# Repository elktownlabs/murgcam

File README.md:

# murgcam
Autonomous, time-based, low power still camera.

The first instance of this camera in action:
https://wwv-schwarzwald.de/die-murg/cam

## Project description
This repo documents Hard- and Software for a very low-power, battery/solar powered camera with GSM/LTE connectivity.
It is designed to operate unattended for months in an off-grid environment.
It will upload images to a server on a time-based trigger.

The intended use-case is to monitor river-waterlevels for whitewater paddlers. 
The advantage of a camera over other gauging techniques 
is, only line-of sight is needed, no access to the Water.
Being diectly at the water brings legal and mechanical challenginges that are not at play using a camera.

Full discussion of the original design decisions here:
https://elktown-labs.com/autonomouscam/

## Status
The repo just transferred from non-public to public, we try to add more documentation.
Currently, work is going on for a new hardware revision with a few improvements, most notably upgrading to a LTE capable Modem.

## Participation welcome
If you are interested in building / operating such a camera or want to contribute to it's development,
feel free to open an [issue](https://github.com/elktownlabs/murgcam/issues).

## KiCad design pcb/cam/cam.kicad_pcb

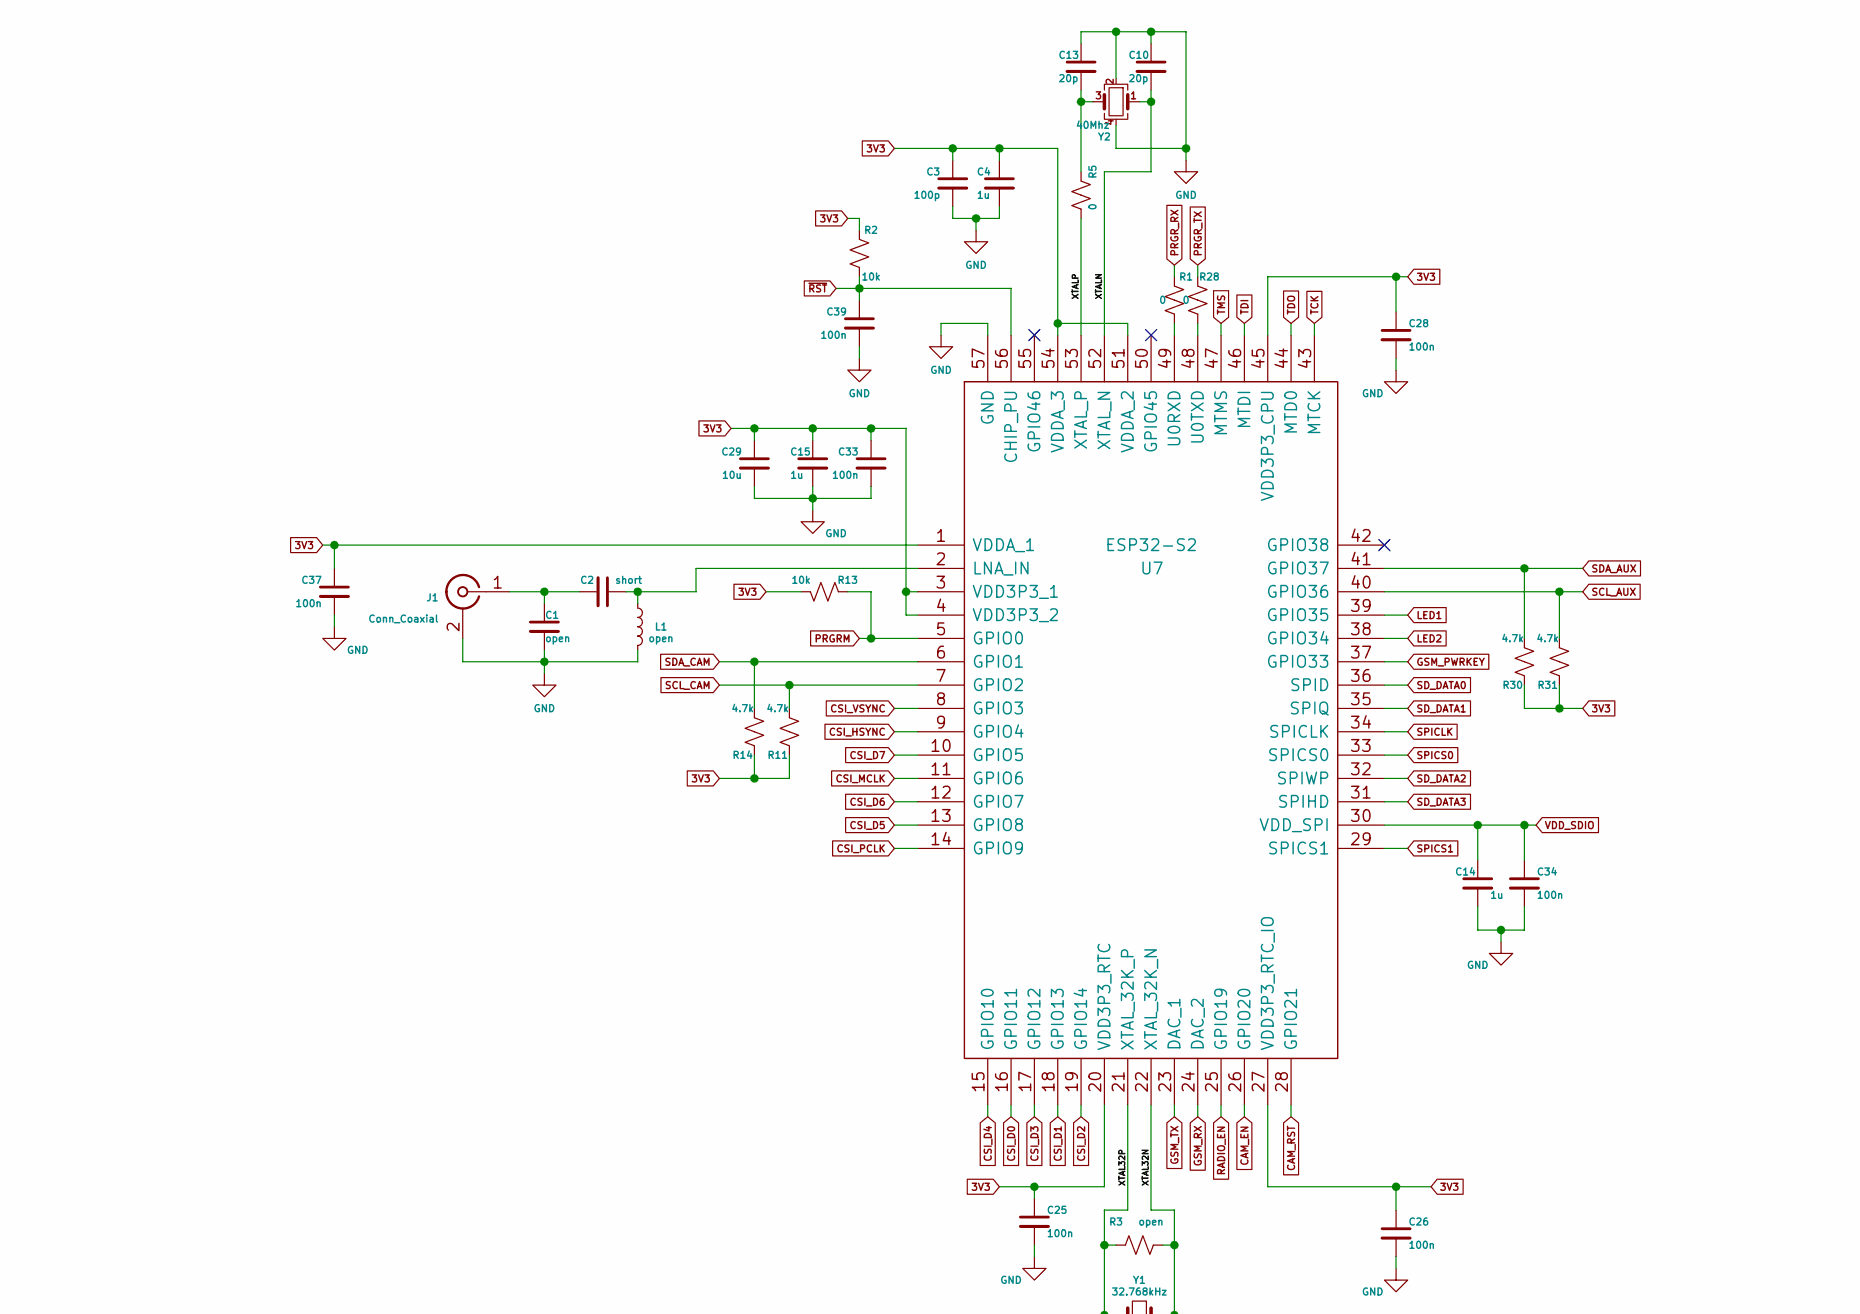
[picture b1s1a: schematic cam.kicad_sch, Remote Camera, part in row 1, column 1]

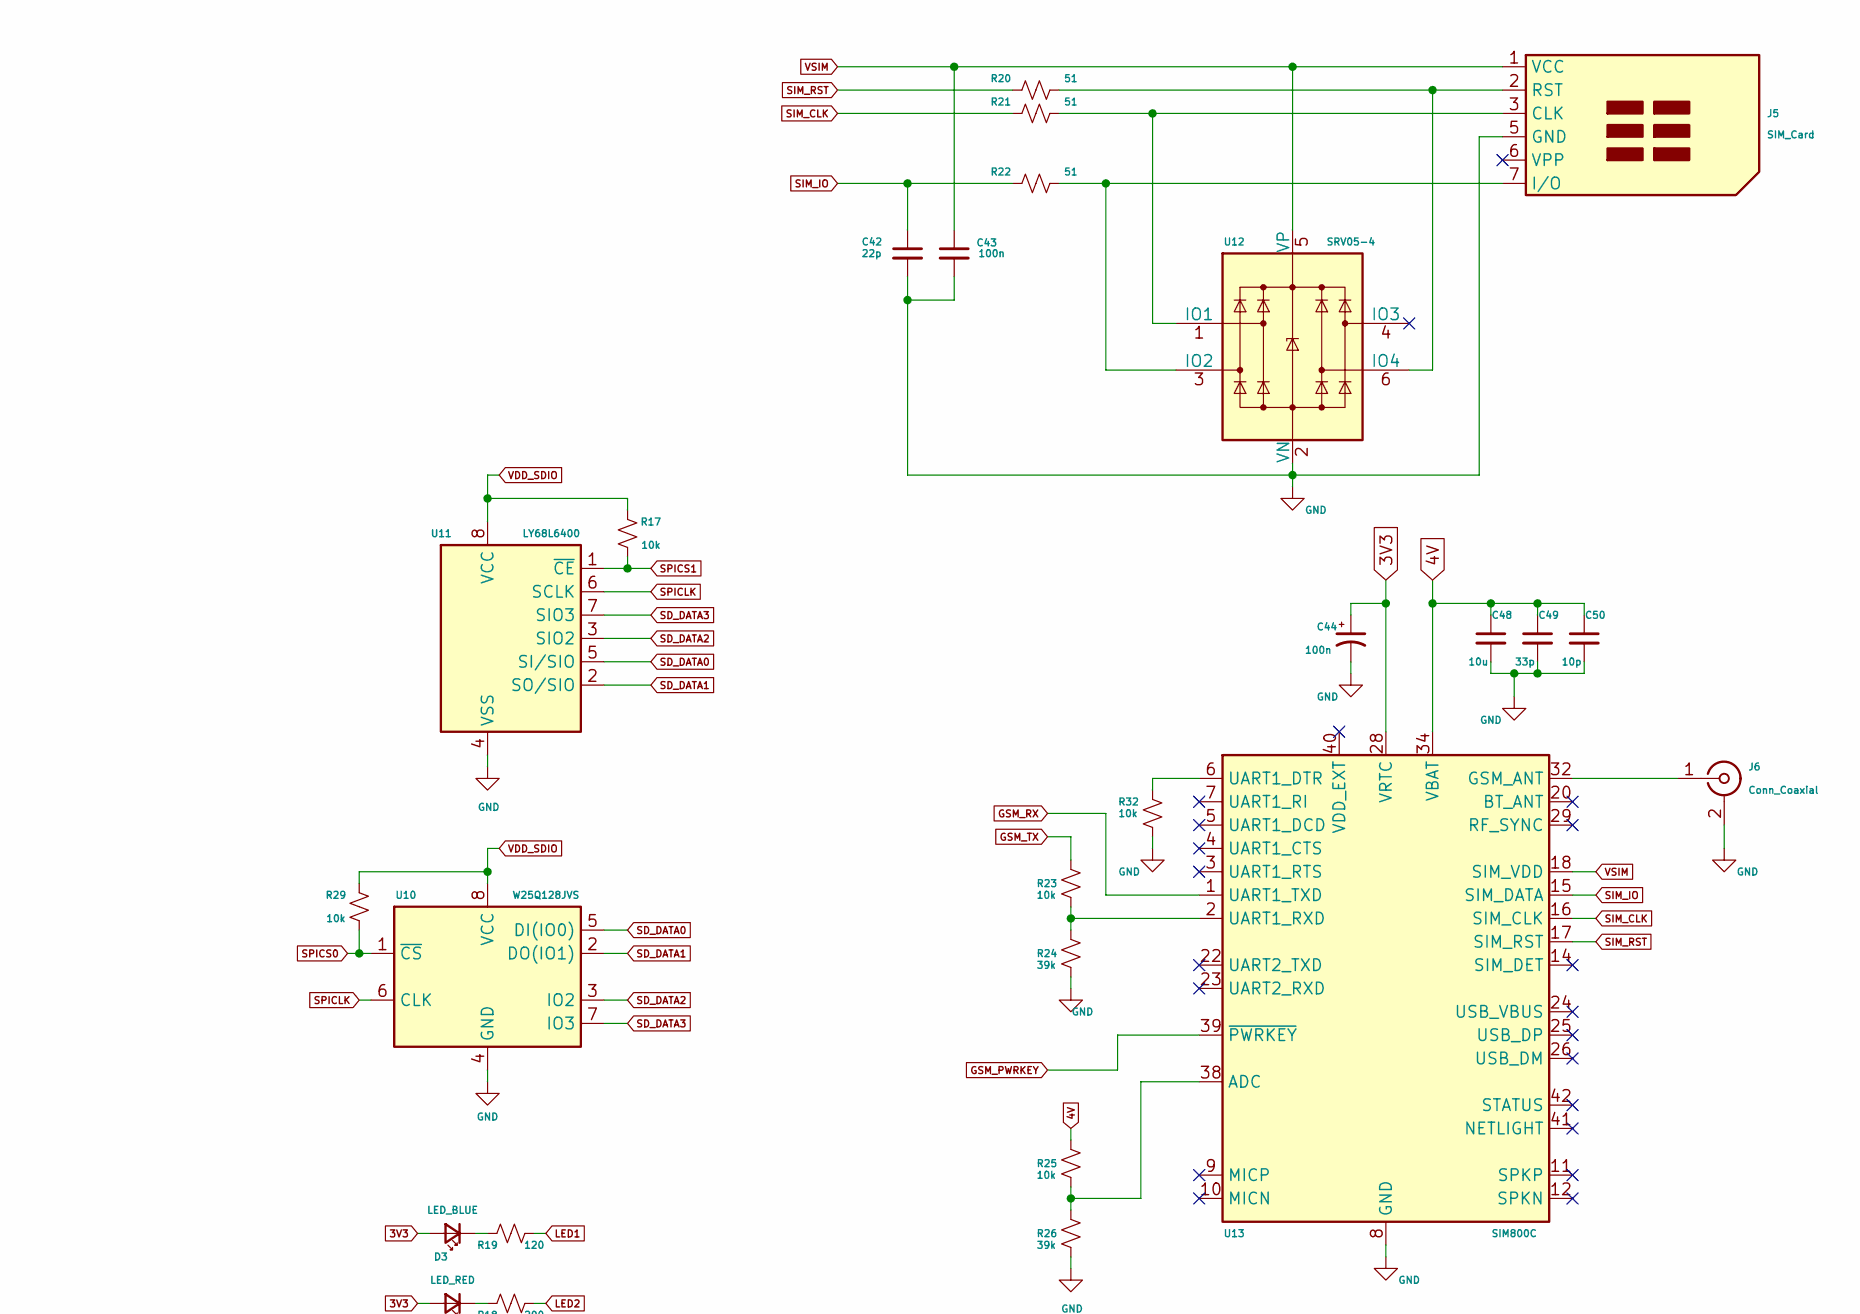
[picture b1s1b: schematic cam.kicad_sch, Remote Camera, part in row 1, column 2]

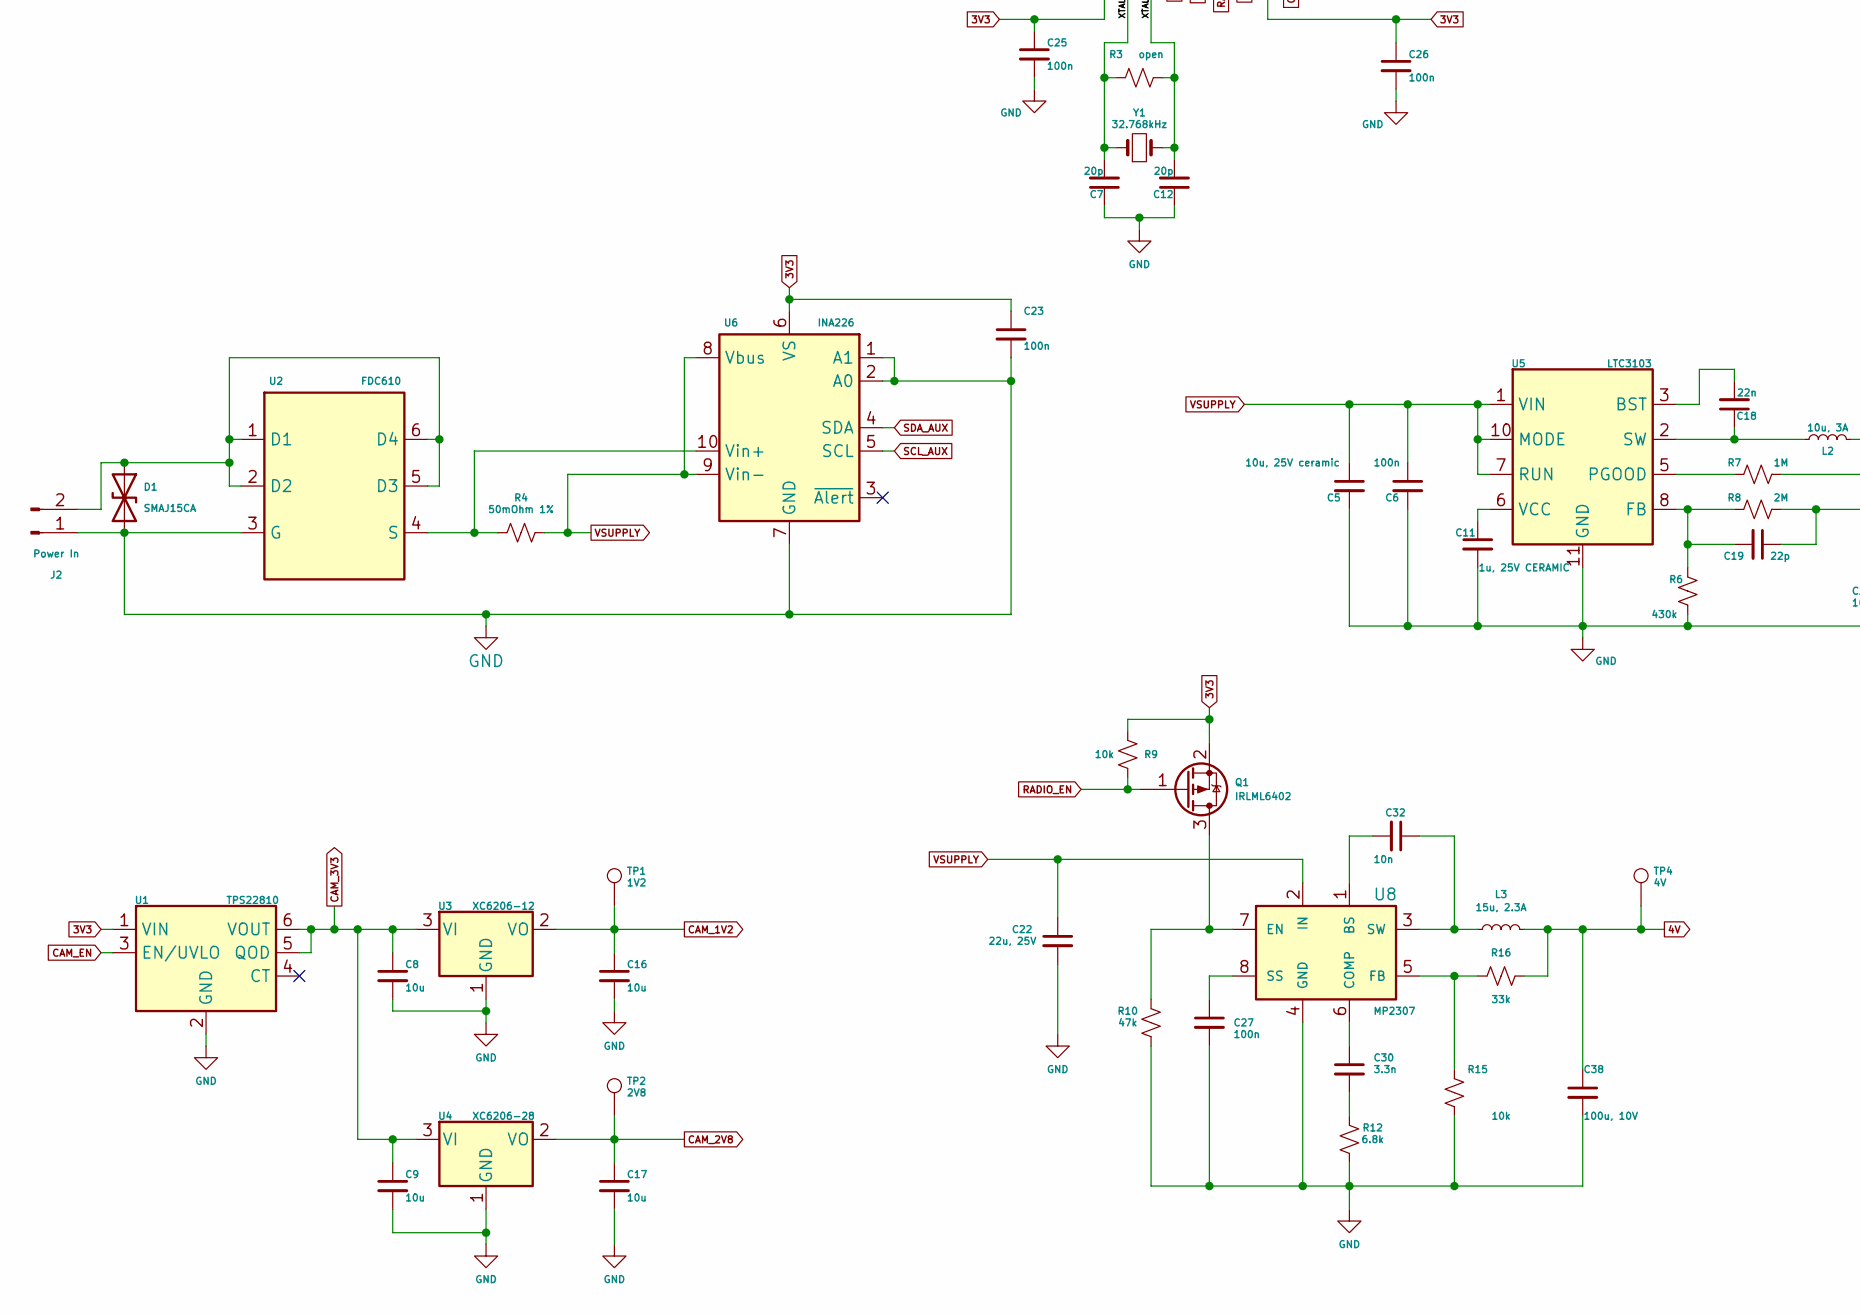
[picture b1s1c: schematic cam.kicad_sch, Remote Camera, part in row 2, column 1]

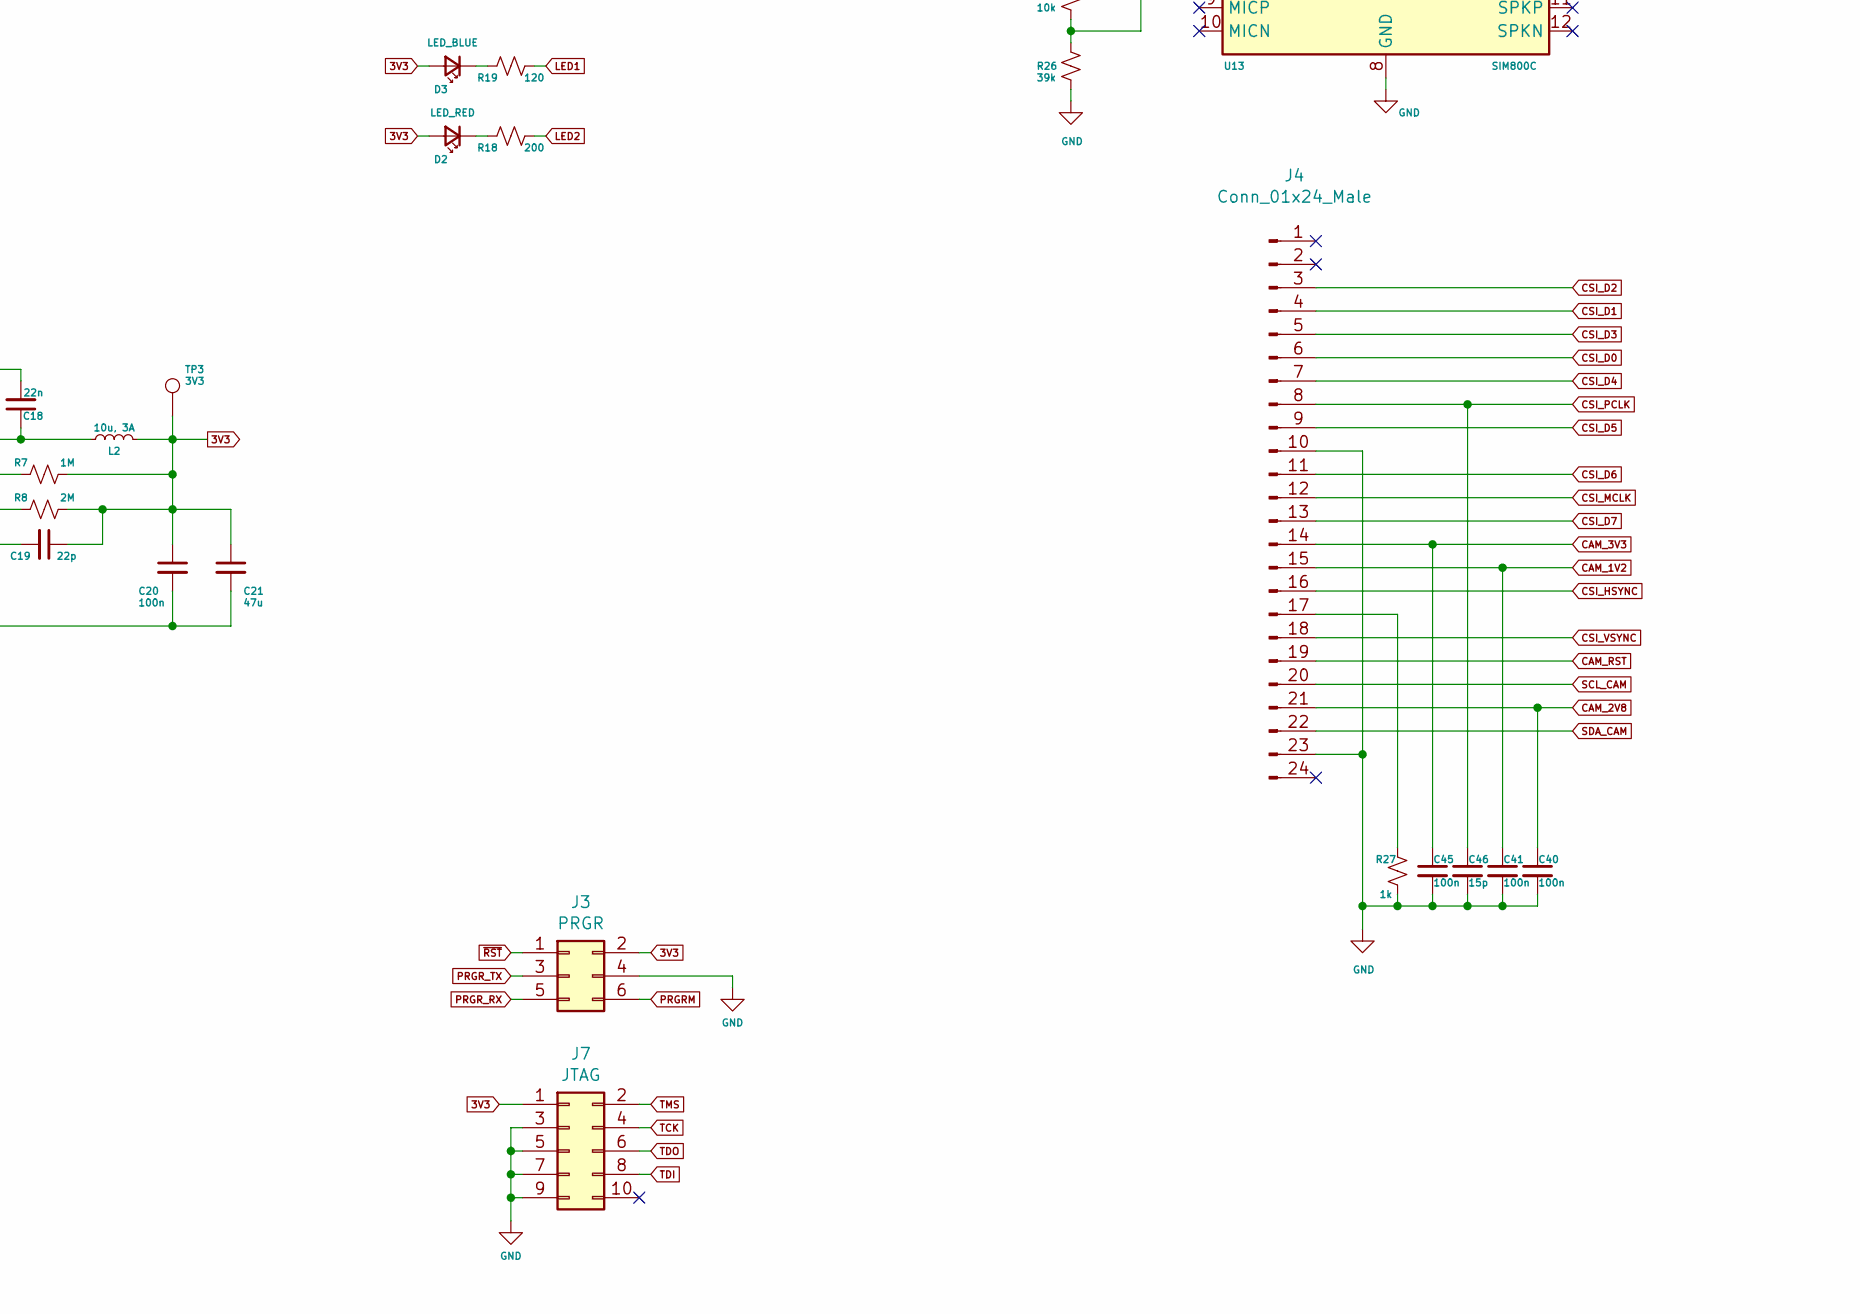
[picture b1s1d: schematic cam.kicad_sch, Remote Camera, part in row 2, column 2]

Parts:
C1: open; C_0603_1608Metric
C2: short; C_0603_1608Metric
C3: 100p; C_0603_1608Metric
C4, C14, C15: 1u; C_0603_1608Metric
C5: 10u, 25V ceramic; C_1210_3225Metric
C6, C20, C23, C25, C26, C27, C28, C33, C34, C37, C39, C40, C41, C43, C44, C45: 100n; C_0603_1608Metric
C7, C10, C12, C13: 20p; C_0603_1608Metric
C8, C9, C16, C17, C29, C48: 10u; C_0805_2012Metric
C11: 1u, 25V CERAMIC; C_0805_2012Metric
C18: 22n; C_0603_1608Metric
C19, C42: 22p; C_0603_1608Metric
C21: 47u; C_1206_3216Metric
C22: 22u, 25V; C_1210_3225Metric
C30: 3.3n; C_0603_1608Metric
C32: 10n; C_0603_1608Metric
C38: 100u, 10V; C_1206_3216Metric
C46: 15p; C_0603_1608Metric
C49: 33p; C_0603_1608Metric
C50: 10p; C_0603_1608Metric
D1: SMAJ15CA; D_SMA
D2: LED_RED; LED_0603_1608Metric
D3: LED_BLUE; LED_0603_1608Metric
J1, J6: Conn_Coaxial; U.FL_Hirose_U.FL-R-SMT-1_Vertical
J2: Power In; JST_XH_B2B-XH-A_1x02_P2.50mm_Vertical
J3: PRGR; PinHeader_2x03_P1.27mm_Vertical
J4: Conn_01x24_Male; Hirose_FH12-24S-0.5SH_1x24-1MP_P0.50mm_Horizontal
J5: SIM_Card; MicroSim_6P
J7: JTAG; PinHeader_2x05_P1.27mm_Vertical
L1: open; L_0603_1608Metric
L2: 10u, 3A; IND_LPS3314-222MRC
L3: 15u, 2.3A; MSS7348-XXXMEC
Q1: IRLML6402; SOT-23
R1, R28: 0; R_0603_1608Metric
R2, R9, R13, R15, R17, R23, R25, R29, R32: 10k; R_0603_1608Metric
R3: open; R_0603_1608Metric
R4: 50mOhm 1%; L_1206_3216Metric
R5: 0; L_0603_1608Metric
R6: 430k; R_0603_1608Metric
R7: 1M; R_0603_1608Metric
R8: 2M; R_0603_1608Metric
R10: 47k; R_0603_1608Metric
R11, R14, R30, R31: 4.7k; R_0603_1608Metric
R12: 6.8k; R_0603_1608Metric
R16: 33k; R_0603_1608Metric
R18: 200; R_0603_1608Metric
R19: 120; R_0603_1608Metric
R20, R21, R22: 51; R_0603_1608Metric
R24, R26: 39k; R_0603_1608Metric
R27: 1k; R_0603_1608Metric
TP1: 1V2; TestPoint_Loop_D2.60mm_Drill0.9mm_Beaded
TP2: 2V8; TestPoint_Loop_D2.60mm_Drill0.9mm_Beaded
TP3: 3V3; TestPoint_Loop_D2.60mm_Drill0.9mm_Beaded
TP4: 4V; TestPoint_Loop_D2.60mm_Drill0.9mm_Beaded
U1: TPS22810; SOT-23-6
U2: FDC610; TSSOP-8_3x3mm_P0.65mm
U3: XC6206-12; SOT-23
U4: XC6206-28; SOT-23
U5: LTC3103; MSOP-10-1EP_3x3mm_P0.5mm_EP1.68x1.88mm
U6: INA226; VSSOP-10_3x3mm_P0.5mm
U7: ESP32-S2; QFN40P700X700X90-57N-D; Manufacturer_Part_Number ESP32-S2; Mouser Part Number 356-ESP32-S2
U8: MP2307; SOIC-8-1EP_3.9x4.9mm_P1.27mm_EP2.514x3.2mm
U10: W25Q128JVS; SOIC-8_5.23x5.23mm_P1.27mm
U11: LY68L6400; SOIC-8_3.9x4.9mm_P1.27mm
U12: SRV05-4; SOT-23-6
U13: SIM800C; SIMCom_SIM800C
Y1: 32.768kHz; Crystal_SMD_SeikoEpson_MC306-4Pin_8.0x3.2mm
Y2: 40Mhz; Crystal_SMD_5032-4Pin_5.0x3.2mm

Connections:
3V3: C3.1, C4.1, C15.1, C19.1, C20.1, C21.1, C23.1, C25.1, C26.1, C28.1, C29.1, C33.1, C37.1, C44.1, D2.2 (A), D3.2 (A), J3.2, J7.1, L2.2, Q1.2 (S), R2.1, R7.2, R8.2, R9.1, R11.1, R13.2, R14.1, R30.1, R31.1, TP3.1, U1.1 (VIN), U6.6 (VS), U7.1 (VDDA_1), U7.3 (VDD3P3_1), U7.4 (VDD3P3_2), U7.20 (VDD3P3_RTC), U7.27 (VDD3P3_RTC_IO), U7.45 (VDD3P3_CPU), U7.51 (VDDA_2), U7.54 (VDDA_3), U13.28 (VRTC)
4V: C38.1, C48.1, C49.1, C50.1, L3.2, R16.2, R25.1, TP4.1, U13.34 (VBAT), U13.35 (VBAT)
/XTAL32N: C12.2, R3.2, U7.22 (XTAL_32K_N), Y1.2
/XTAL32P: C7.2, R3.1, U7.21 (XTAL_32K_P), Y1.1
/XTALN: C10.2, U7.52 (XTAL_N), Y2.1
/XTALP: R5.2, U7.53 (XTAL_P)
CAM_1V2: C16.1, C41.1, J4.15, TP1.1, U3.2 (VO)
CAM_2V8: C17.1, C40.1, J4.21, TP2.1, U4.2 (VO)
CAM_3V3: C8.1, C9.1, C45.1, J4.14, U1.5 (QOD), U1.6 (VOUT), U3.3 (VI), U4.3 (VI)
CAM_EN: U1.3 (EN/UVLO), U7.26 (GPIO20)
CAM_RST: J4.19, U7.28 (GPIO21)
CSI_D0: J4.6, U7.16 (GPIO11)
CSI_D1: J4.4, U7.18 (GPIO13)
CSI_D2: J4.3, U7.19 (GPIO14)
CSI_D3: J4.5, U7.17 (GPIO12)
CSI_D4: J4.7, U7.15 (GPIO10)
CSI_D5: J4.9, U7.13 (GPIO8)
CSI_D6: J4.11, U7.12 (GPIO7)
CSI_D7: J4.13, U7.10 (GPIO5)
CSI_HSYNC: J4.16, U7.9 (GPIO4)
CSI_MCLK: J4.12, U7.11 (GPIO6)
CSI_PCLK: C46.1, J4.8, U7.14 (GPIO9)
CSI_VSYNC: J4.18, U7.8 (GPIO3)
GND: C1.2, C3.2, C4.2, C5.2, C6.2, C7.1, C8.2, C9.2, C10.1, C11.2, C12.1, C13.1, C14.2, C15.2, C16.2, C17.2, C20.2, C21.2, C22.2, C23.2, C25.2, C26.2, C27.2, C28.2, C29.2, C33.2, C34.2, C37.2, C38.2, C39.2, C40.2, C41.2, C42.2, C43.2, C44.2, C45.2, C46.2, C48.2, C49.2, C50.2, D1.2 (A2), J1.2 (Ext), J2.1, J3.4, J4.10, J4.23, J5.5 (GND), J6.2 (Ext), J7.3, J7.5, J7.7, J7.9, L1.2, R6.1, R10.1, R12.1, R15.1, R24.2, R26.2, R27.1, R32.2, U1.2 (GND), U2.3 (G), U3.1 (GND), U4.1 (GND), U5.4 (GND), U5.11 (GND), U6.1 (A1), U6.2 (A0), U6.7 (GND), U7.57 (GND), U8.4 (GND), U8.9 (GND), U10.4 (GND), U11.4 (VSS), U12.2 (VN), U13.8 (GND), U13.13 (GND), U13.19 (GND), U13.21 (GND), U13.27 (GND), U13.30 (GND), U13.31 (GND), U13.33 (GND), U13.36 (GND), U13.37 (GND), Y2.2, Y2.4
GSM_PWRKEY: U7.37 (GPIO33), U13.39 (~PWRKEY)
GSM_RX: U7.24 (DAC_2), U13.1 (UART1_TXD)
GSM_TX: R23.1, U7.23 (DAC_1)
LED1: R19.1, U7.39 (GPIO35)
LED2: R18.1, U7.38 (GPIO34)
unnamed: C1.1, C2.2, J1.1 (In)
unnamed: C2.1, L1.1, U7.2 (LNA_IN)
unnamed: C11.1, U5.6 (VCC)
unnamed: C13.2, R5.1, Y2.3
unnamed: C18.1, L2.1, U5.2 (SW)
unnamed: C18.2, U5.3 (BST)
unnamed: C19.2, R6.2, R8.1, U5.8 (FB)
unnamed: C27.1, U8.8 (SS)
unnamed: C30.1, U8.6 (COMP)
unnamed: C30.2, R12.2
unnamed: C32.1, L3.1, U8.3 (SW)
unnamed: C32.2, U8.1 (BS)
unnamed: D1.1 (A1), J2.2, U2.1 (D1), U2.2 (D2), U2.5 (D3), U2.6 (D4)
unnamed: D2.1 (K), R18.2
unnamed: D3.1 (K), R19.2
unnamed: J4.17, R27.2
unnamed: J5.2 (RST), R20.1, U12.6 (IO4)
unnamed: J5.3 (CLK), R21.1, U12.1 (IO1)
unnamed: J5.7 (I/O), R22.1, U12.3 (IO2)
unnamed: J6.1 (In), U13.32 (GSM_ANT)
unnamed: Q1.3 (D), R10.2, U8.7 (EN)
unnamed: R1.2, U7.49 (U0RXD)
unnamed: R4.1, U2.4 (S), U6.10 (Vin+)
unnamed: R7.1, U5.5 (PGOOD)
unnamed: R15.2, R16.1, U8.5 (FB)
unnamed: R23.2, R24.1, U13.2 (UART1_RXD)
unnamed: R25.2, R26.1, U13.38 (ADC)
unnamed: R28.2, U7.48 (U0TXD)
unnamed: R32.1, U13.6 (UART1_DTR)
PRGRM: J3.6, R13.1, U7.5 (GPIO0)
PRGR_RX: J3.5, R1.1
PRGR_TX: J3.3, R28.1
RADIO_EN: Q1.1 (G), R9.2, U7.25 (GPIO19)
SCL_AUX: R31.2, U6.5 (SCL), U7.40 (GPIO36)
SCL_CAM: J4.20, R11.2, U7.7 (GPIO2)
SDA_AUX: R30.2, U6.4 (SDA), U7.41 (GPIO37)
SDA_CAM: J4.22, R14.2, U7.6 (GPIO1)
SD_DATA0: U7.36 (SPID), U10.5 (DI(IO0)), U11.5 (SI/SIO)
SD_DATA1: U7.35 (SPIQ), U10.2 (DO(IO1)), U11.2 (SO/SIO)
SD_DATA2: U7.32 (SPIWP), U10.3 (IO2), U11.3 (SIO2)
SD_DATA3: U7.31 (SPIHD), U10.7 (IO3), U11.7 (SIO3)
SIM_CLK: R21.2, U13.16 (SIM_CLK)
SIM_IO: C42.1, R22.2, U13.15 (SIM_DATA)
SIM_RST: R20.2, U13.17 (SIM_RST)
SPICLK: U7.34 (SPICLK), U10.6 (CLK), U11.6 (SCLK)
SPICS0: R29.1, U7.33 (SPICS0), U10.1 (~CS)
SPICS1: R17.1, U7.29 (SPICS1), U11.1 (~CE)
TCK: J7.4, U7.43 (MTCK)
TDI: J7.8, U7.46 (MTDI)
TDO: J7.6, U7.44 (MTD0)
TMS: J7.2, U7.47 (MTMS)
VDD_SDIO: C14.1, C34.1, R17.2, R29.2, U7.30 (VDD_SPI), U10.8 (VCC), U11.8 (VCC)
VSIM: C43.1, J5.1 (VCC), U12.5 (VP), U13.18 (SIM_VDD)
VSUPPLY: C5.1, C6.1, C22.1, R4.2, U5.1 (VIN), U5.7 (RUN), U5.10 (MODE), U6.8 (Vbus), U6.9 (Vin-), U8.2 (IN)
~RST: C39.1, J3.1, R2.2, U7.56 (CHIP_PU)

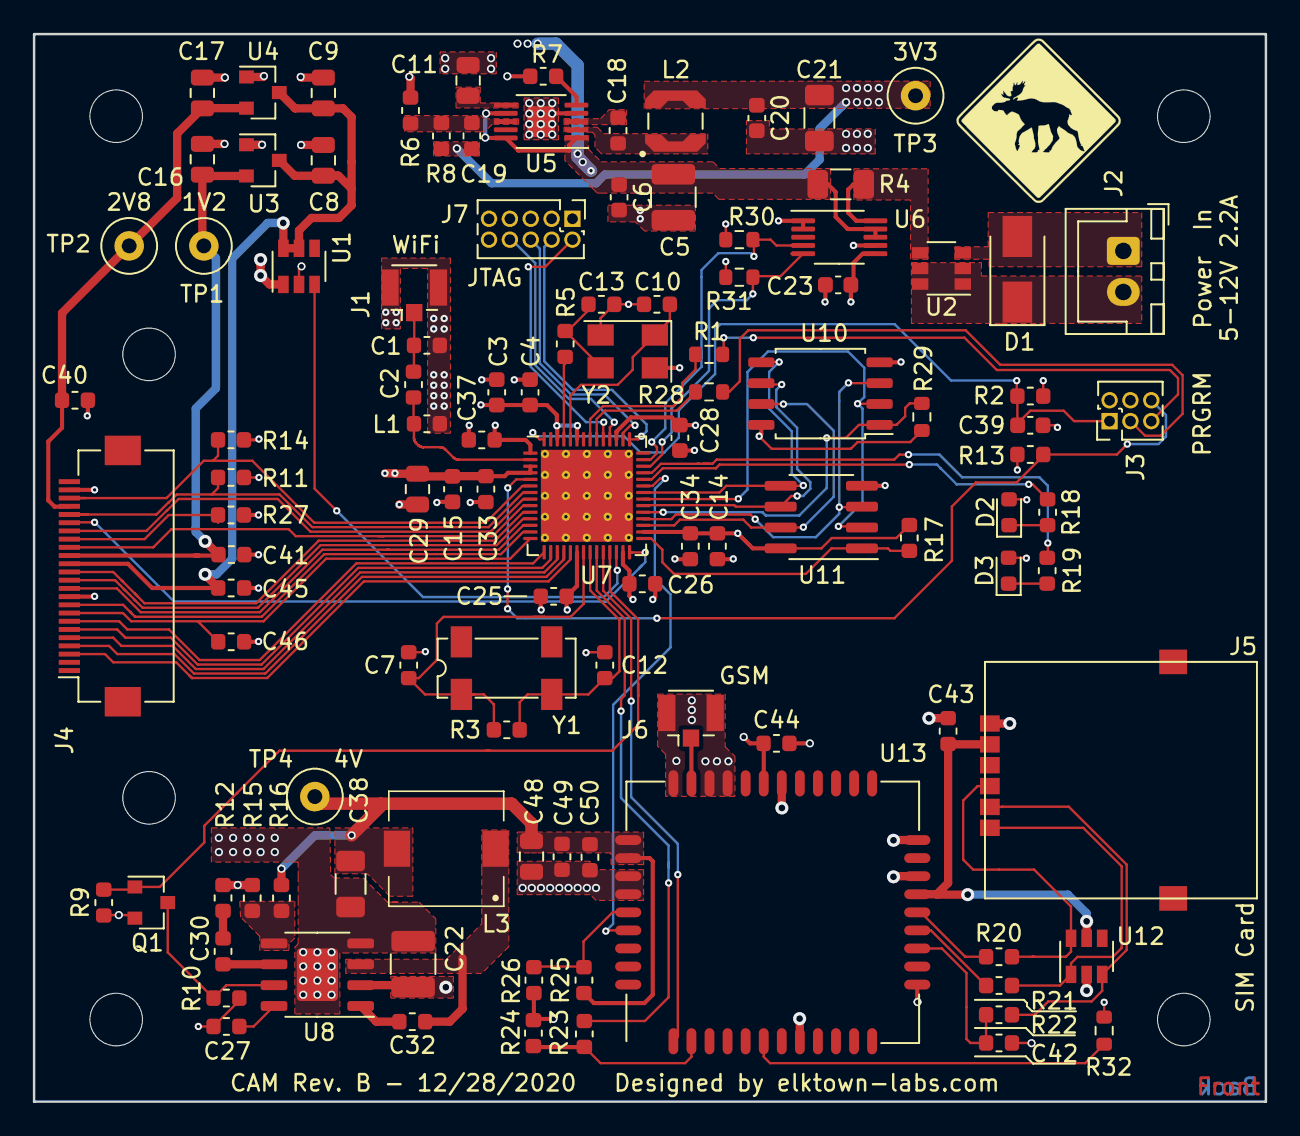
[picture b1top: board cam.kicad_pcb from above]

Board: 4 copper layers, 75.0 x 65.0 mm, 109 parts (0 on the bottom side), 84 nets.

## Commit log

2020-12-27 Finished PCB for ESP32-S2
2020-12-27 Minor fixed to ESP-S2 pcb
2020-12-27 More optimizations to pcb
2020-12-27 Fixed connection / layout of flash / ram chips
2020-12-28 More fixes to pcb
2021-01-26 Finished revision 1
2021-03-17 Added BOM sheet for manual population; Updated PCB
2021-04-04 Added web-gui
2021-04-04 finished pcb revision b
2021-04-04 Added firmware
2021-04-04 Small changes to pcb
2021-04-04 Added 3D model for possible lens holder
2021-04-04 Deleted old pcb; renamed discrete esp-s2 pcb to pcb
2021-04-04 Removed old files
2021-04-04 Added web backend
2021-04-04 Added .gitignore to firmware
2021-04-04 Fixed length of nvs keys; fixed wrong 'firmware' json key
2021-04-07 web-if: Added version number; Fixed config file to automatically detect production environment
2021-04-12 Added error-handling and retried for camera handling
2021-04-13 Added draft html page for esp32 web frontend
2021-04-14 Added configuration web page
2021-04-14 Added cad parts and web frontend
2021-04-14 added cad libraries
2021-04-17 Fixed camera settings; Added hue and saturation settings
2021-04-21 Backend: Added base64 photo mode
2021-04-24 Upped version to 0.0.3; Added current settings to json sent to server
2021-05-01 Changed 3d model for camera holder
2021-05-02 Completed camera settings interface
2021-06-05 Firmware: Improved timout; Upped to 0.0.4
2021-06-07 Firmware: Many fixes. Camera more stable; Modem more stable
2021-06-07 Firmware: Removed fixed quality setting
2021-06-23 Minor changes
2021-07-09 Firmware: Fixed camera access
2021-07-21 Added user database
2021-07-21 Backend cleaned up; Moved upload script to api directory
2021-07-22 Config mode can now be reached by turning off power at a certain time
2021-07-23 Fixed logging messages
2021-07-23 Fixed software version information
2021-07-24 renamed user db to settings db; added camera settings to db; added full name to json return structure of authenticate.php
2021-07-24 Extended upload.php to create public, watermarked version of photo
2021-07-24 Url now taken from config and no longer hardcoded; partition for firmware now 4MB
2021-07-27 Added pixel timing function for exposure control; Fixed PAP/CHAP mixup in web-ui
2021-08-19 Added narrow base for battery and camera
2021-08-19 Added minimum voltage check on startup
2021-08-19 Increased number of retries for modem connection
2021-08-19 Backend URL now configurable
2021-08-19 sdkconfig updated by idf toolchain
2021-08-31 Vue frontend: Added missing dependencies
2021-08-31 Vue frontend: Many changes. Nothing is completely done yet. Made forms more usable; New form for update frequency; Multi-user-mode added
2021-08-31 vue frontend: Transitioning to new api; user id/avatar stuff added; pixel timing option added
2021-09-01 Vue frontend: Added new values to SettingsForm; SettingsForm cleanups
2021-09-01 Vue frontend: implemented user rights; many updates; more functions
2021-09-02 Vue frontend: Small device app nav menu now hides options the user has no rights for.
2021-09-02 Test upload: Created sub-project; added test card
2021-09-02 Web Backend: Cleand up db directory
2021-09-02 Web Backend: Updated database schemas / sqlite files
2021-09-02 Web Backend: updated api functions
2021-09-03 Web-Backend: Added cleanup script for linux and systemd service/timer definitions
2021-09-03 Vue Frontend: Added base path to vue-router in production environment
2021-09-03 Updated .env.* to reflect current api locations
2021-09-03 Vue frontend: Added graceful handling of expired sessions; login now possible with return key
2021-09-03 Vue Frontend: Changed name from WebCam to MurgCam; changed favicon
2021-09-03 Added test upload script
2021-09-03 Vue Frontend: Fixed frequency form
2021-09-03 Upload tester: Added newline character
2021-09-03 Web Backend: Finished implementing upload.sh; many improvements to api
2021-09-03 Backend: Added config.php
2021-09-03 Vue Frontend: Updated colors
2021-09-04 Backend: fixed bug in get_frequency
2021-09-05 Added additonal guards to make sure time to sleep does not overflow when sleep time is lower than time alive
2021-09-05 Firmware: Added camera settle time after cam settings have been modified
2021-09-05 Web Backend: updated directories for production; time-out interval fixed when camera starts to early; upload receiver picture management updated
2021-09-05 Firmware: updated sdk config
2021-09-05 Firmware: increased upload timeout; set settle time for cam to 4secs
2021-09-05 Web backend: added new api commands: photo_delete, photo_newavailable
2021-09-05 Vue Backend: Upped to v0.4; added delete function; fixed time zones in photo browser; add notification about new photos
2021-12-01 New functionality: creation of an 800x600 photo for the public site
2021-12-05 Backend: fixed get_frequency: Scheduled mode switch was not shown correctly
2021-12-05 Web-If: upped version to 0.5
2021-12-07 Updated server to reflect production settings
2022-01-02 Added .gitignore
2022-01-02 Added jsconfig.json
2022-01-02 Added template for displaying hvz gauges
2022-01-02 Upped version to 0.6
2022-01-02 Added hvz-scraper
2022-01-02 working on daemon detachment
2022-01-02 More work on hvz scraper
2022-01-02 Removed pyinstaller from requirements.txt
2022-01-02 Fixed some stuff for deployment; created service file
2022-01-02 Fixed time conversion
2022-01-03 Backend: Added api for gauge querying
2022-01-03 web-if: Added hvz gauges to display
2022-01-03 web-if: Fixed gauge displays
2022-01-08 Web Backend: more bug fixes
2022-06-04 PCB: VSupply track now connects to all supply pins
2022-06-04 Removed old, unused 3d drawings
2022-06-04 Lots of cleanup; Added bom;
2022-06-24 Added it4paddlers/rivermap api
2022-08-03 PCB: Updated values of some components
2022-11-24 Added infos about the used lens and lens holder
2022-11-25 Added infos about the power source
2022-12-03 Web-If: Added checkbox for using sunrise/sunset time instead of a fixed time for first and last photo of the day.
2022-12-03 Added note about sim cards without a PIN to user interface.
2022-12-07 web-backend: changed upload.php to be compatible with php8
2022-12-07 firmware: enabled data connections when sim card is in roaming mode
2022-12-07 web-backend: added missing file
2022-12-09 web-backend: authenticate.php spewed warnings which broke the json output; fixed master login
2022-12-22 fixed admin login; moved user/rights verification to a common php include file.
2022-12-27 web-if: Added config options for sunset/sunrise based photo timing.
2022-12-27 web-backend: Implemented sunset/sunrise dependent picture sequence in upload script. Not fully tested yet.
2022-12-27 web-if: Upped version in package.json to 0.7.0
2023-03-14 Implemented refphoto function in rivermap api
2023-03-14 Replaced reference image for Murg low water as suggested by Jule
2023-08-24 Migrated to KiCad7
